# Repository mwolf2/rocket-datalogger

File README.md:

# rocket-datalogger
Linux-based datalogger for amateur rockets. School project by Max Wolf and Emmett Hart.
Goal -- Make a datalogger that enables amateur rockets to act as low-altitude sounding rockets for meteorological and kinematic data.
Current Status -- Done (for now, might reopen at some point in the future); Contributions Welcome! (please make a pull request)

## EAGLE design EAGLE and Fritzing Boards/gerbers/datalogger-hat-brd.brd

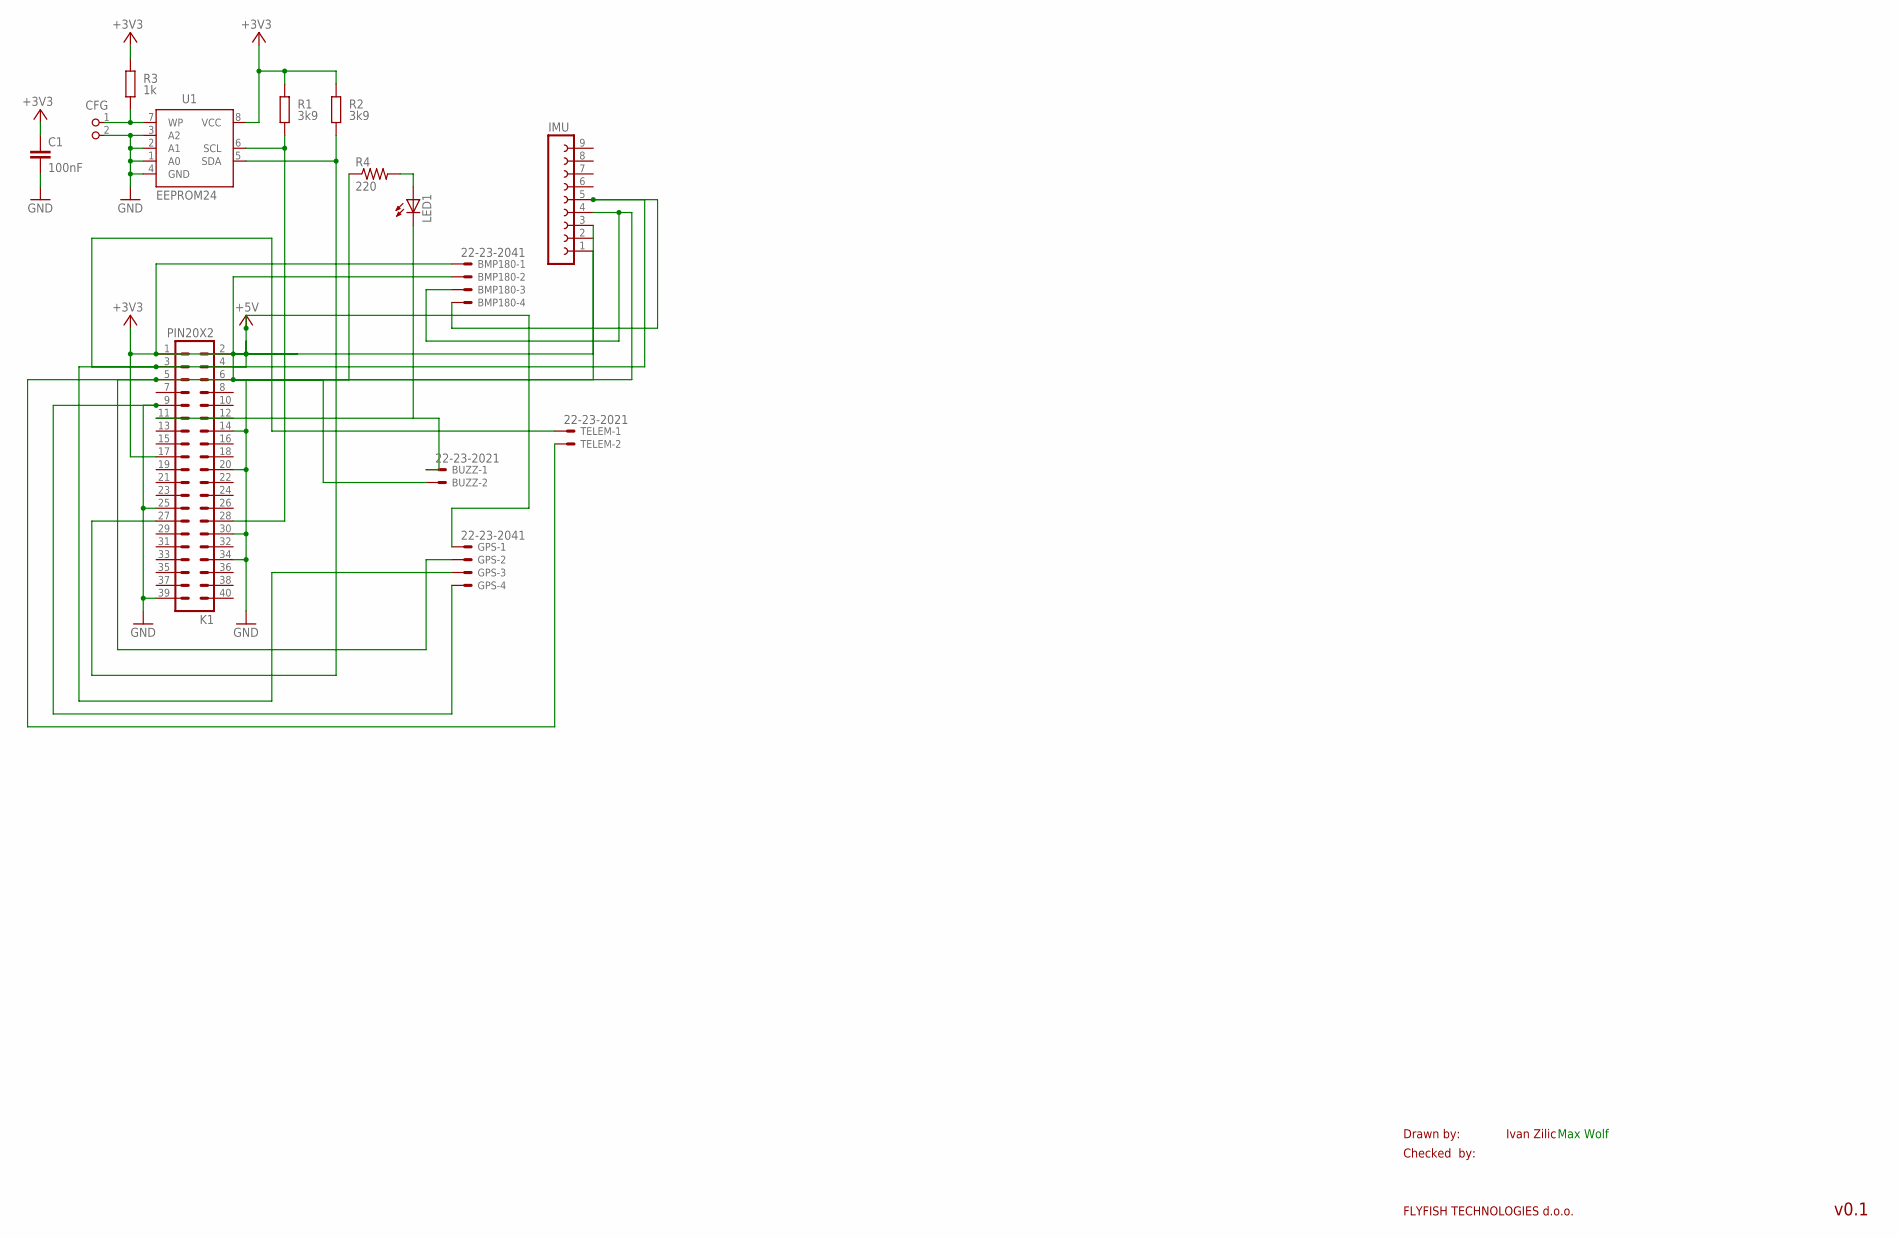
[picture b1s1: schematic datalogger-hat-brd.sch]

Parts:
BMP180: 22-23-2041
BUZZ: 22-23-2021
C1: 100nF; C0805K
CFG: PIN2_100; PIN_W_2
GPS: 22-23-2041
IMU: FE09-1; FE09
K1: PIN20X2; PIN_20X2
LED1: LED_ELD260; LED_LD260
R1, R2: 3k9; M0805; TOLERANCE 5%
R3: 1k; M0805; TOLERANCE 5%
R4: 220; 0204/5
TELEM: 22-23-2021
U1: EEPROM24; SOIC8

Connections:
+3V3: BMP180.1, C1.1, IMU.1, K1.1, K1.17, R1.2, R2.2, R3.2, U1.8 (VCC)
+5V: GPS.1, K1.2, K1.4
GND: BMP180.2, BUZZ.2, C1.2, CFG.2, GPS.4, IMU.3, K1.6, K1.9, K1.14, K1.20, K1.25, K1.30, K1.34, K1.39, R4.1, U1.1 (A0), U1.2 (A1), U1.3 (A2), U1.4 (GND)
unnamed: K1.28, R1.1, U1.6 (SCL)
unnamed: K1.27, R2.1, U1.5 (SDA)
unnamed: CFG.1, R3.1, U1.7 (WP)
unnamed: BMP180.4, GPS.3, IMU.5, K1.3, TELEM.1
unnamed: BMP180.3, GPS.2, IMU.4, K1.5, TELEM.2
unnamed: BUZZ.1, K1.11, LED1.K (C)
unnamed: LED1.A, R4.2

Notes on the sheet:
Drawn by:
Checked by:
FLYFISH TECHNOLOGIES d.o.o.
Ivan Zilic
v0.1
Max Wolf

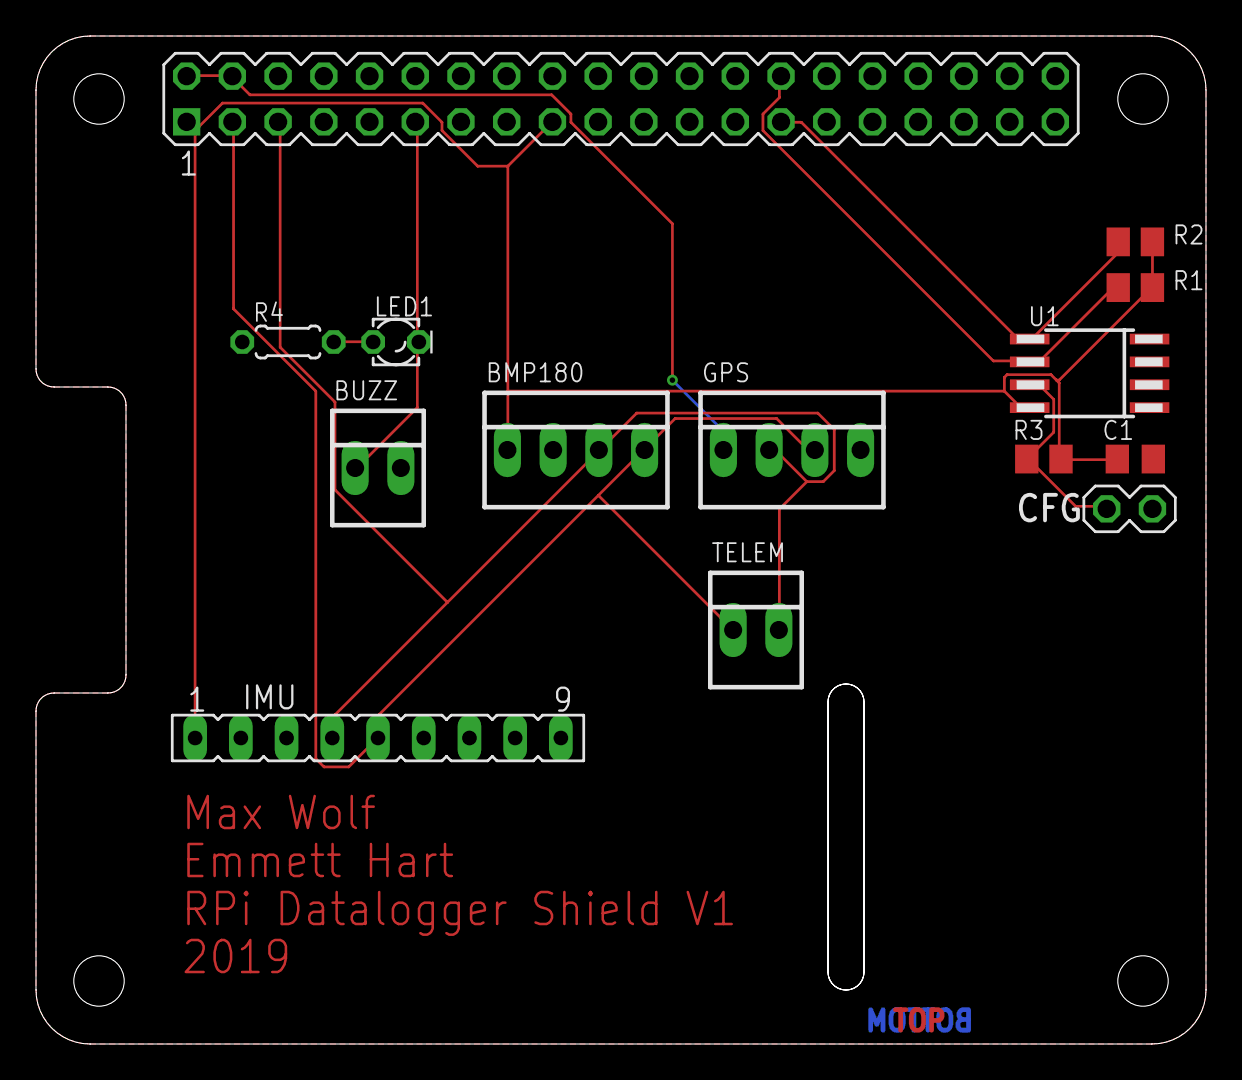
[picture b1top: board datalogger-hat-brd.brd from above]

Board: 2 copper layers, 65.0 x 56.0 mm, 14 parts (0 on the bottom side), 10 nets.

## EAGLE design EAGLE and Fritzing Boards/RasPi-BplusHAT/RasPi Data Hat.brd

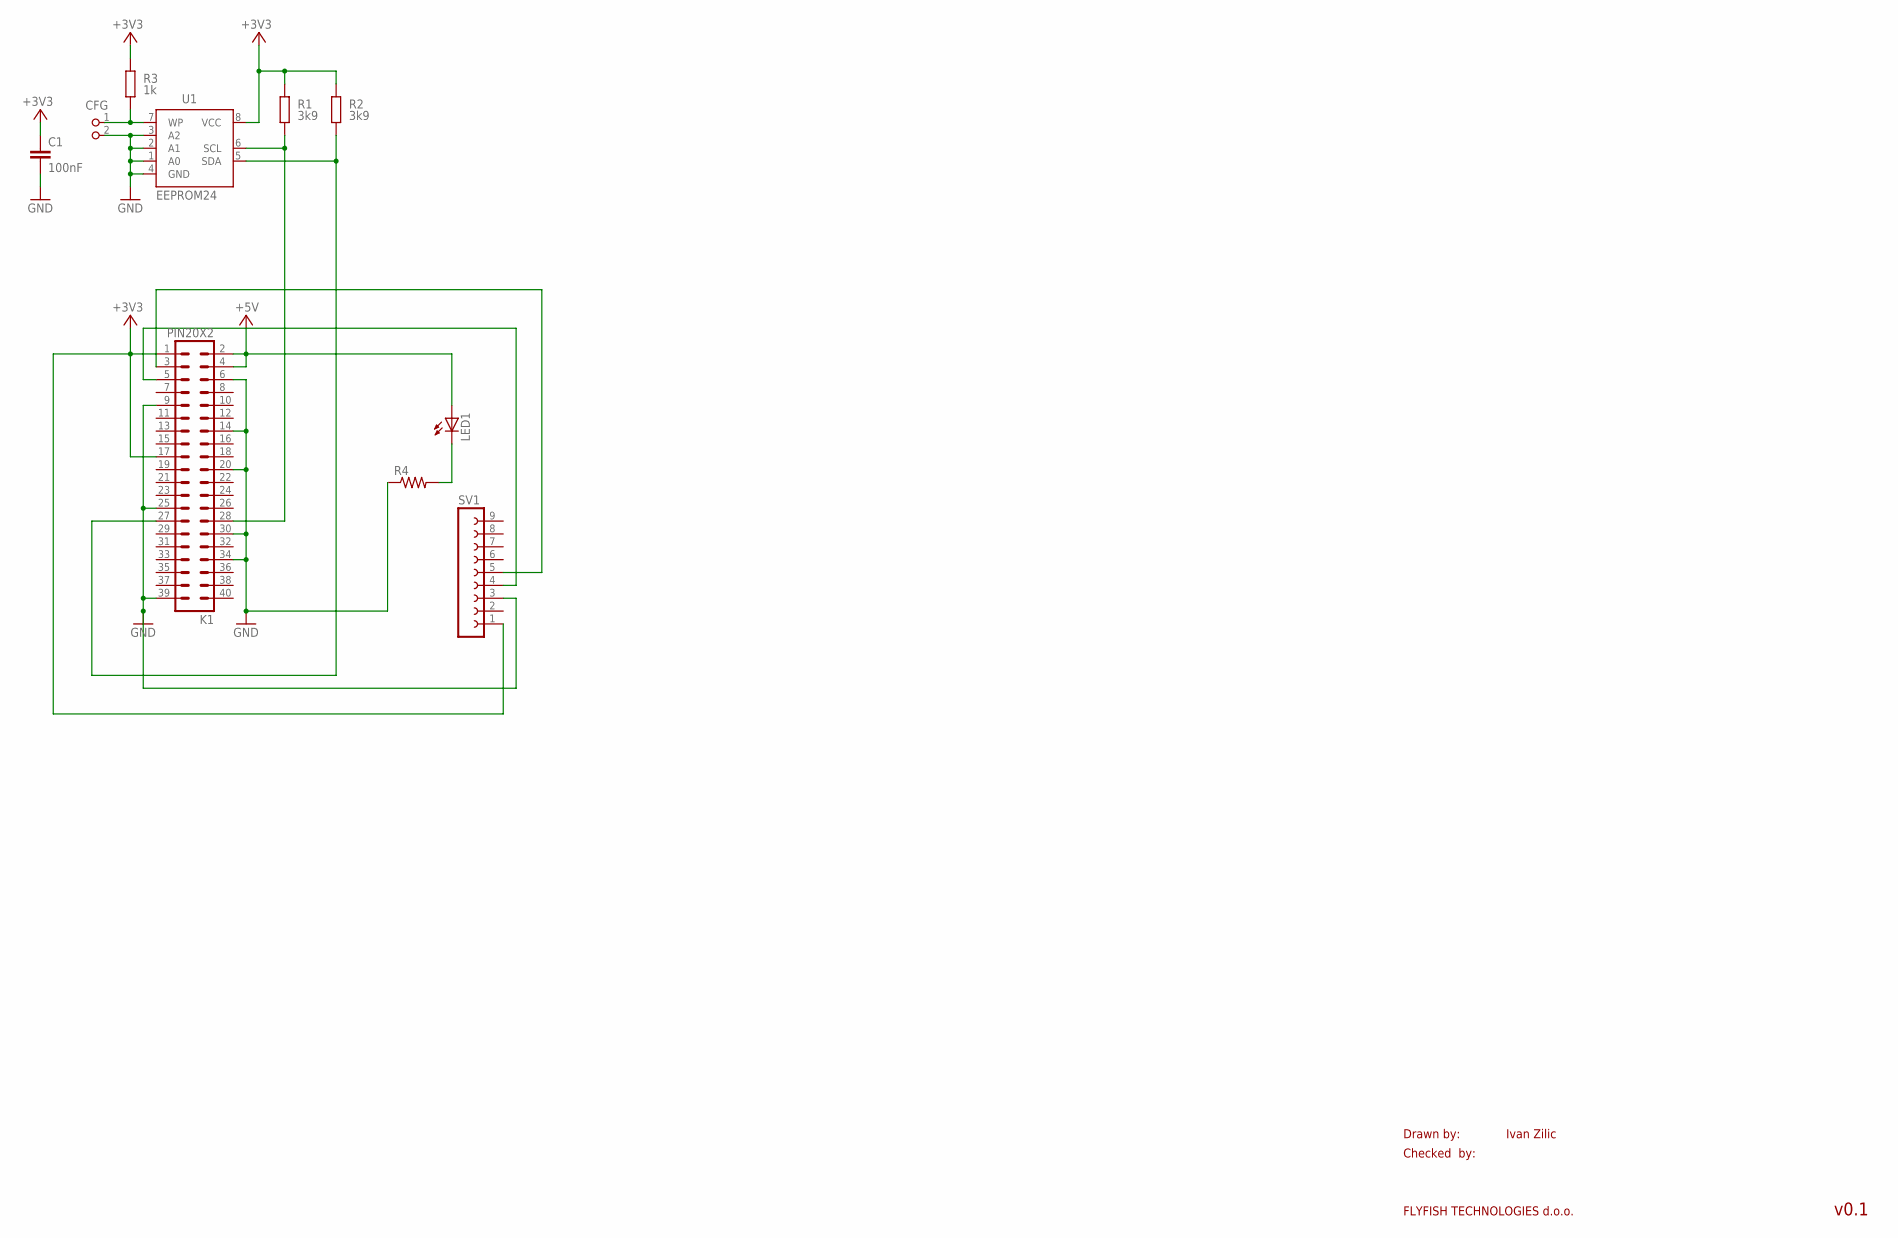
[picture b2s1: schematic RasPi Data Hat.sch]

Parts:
C1: 100nF; C0805K
CFG: PIN2_100; PIN_W_2
K1: PIN20X2; PIN_20X2
LED1: LED3MM
R1, R2: 3k9; M0805; TOLERANCE 5%
R3: 1k; M0805; TOLERANCE 5%
R4: R-US_0204/5; 0204/5
SV1: FE09-1; FE09
U1: EEPROM24; SOIC8

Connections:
+3V3: C1.1, K1.1, K1.17, R1.2, R2.2, R3.2, SV1.1, U1.8 (VCC)
+5V: K1.2, K1.4, LED1.A
GND: C1.2, CFG.2, K1.6, K1.9, K1.14, K1.20, K1.25, K1.30, K1.34, K1.39, R4.1, SV1.3, U1.1 (A0), U1.2 (A1), U1.3 (A2), U1.4 (GND)
unnamed: K1.28, R1.1, U1.6 (SCL)
unnamed: K1.27, R2.1, U1.5 (SDA)
unnamed: CFG.1, R3.1, U1.7 (WP)
unnamed: LED1.K (C), R4.2
unnamed: K1.5, SV1.4
unnamed: K1.3, SV1.5

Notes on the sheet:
Drawn by:
Checked by:
FLYFISH TECHNOLOGIES d.o.o.
Ivan Zilic
v0.1

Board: 2 copper layers, 10 parts (0 on the bottom side), 9 nets, no tracks yet.

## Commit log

2019-04-27 Add files via upload
    First project commit outside of when repository was created. Includes EAGLE and Fritzing boards, images, and programs as of 4/27/2019 at 11:33AM GMT
2019-04-28 Add files via upload
    Committed more recent files to master branch, and not in .zip format. 5:18PM GMT
2019-05-01 Rename EAGLE and Fritzing Boards/copper_bottom.gbr to EAGLE and Fritzing Boards/gerbers/copper_bottom.gbr
2019-05-01 Rename EAGLE and Fritzing Boards/copper_top.gbr to EAGLE and Fritzing Boards/gerbers/copper_top.gbr
2019-05-01 Rename EAGLE and Fritzing Boards/datalogger-hat-brd.brd to EAGLE and Fritzing Boards/gerbers/datalogger-hat-brd.brd
2019-05-01 Rename EAGLE and Fritzing Boards/datalogger-hat-brd.sch to EAGLE and Fritzing Boards/gerbers/datalogger-hat-brd.sch
2019-05-01 Rename EAGLE and Fritzing Boards/drills.xln to EAGLE and Fritzing Boards/gerbers/drills.xln
2019-05-01 Rename EAGLE and Fritzing Boards/gerber_job.gbrjob to EAGLE and Fritzing Boards/gerbers/gerber_job.gbrjob
2019-05-01 Rename EAGLE and Fritzing Boards/profile.gbr to EAGLE and Fritzing Boards/gerbers/profile.gbr
2019-05-01 Rename EAGLE and Fritzing Boards/silkscreen_bottom.gbr to EAGLE and Fritzing Boards/gerbers/silkscreen_bottom.gbr
2019-05-01 Rename EAGLE and Fritzing Boards/silkscreen_top.gbr to EAGLE and Fritzing Boards/gerbers/silkscreen_top.gbr
2019-05-01 Rename EAGLE and Fritzing Boards/soldermask_bottom.gbr to EAGLE and Fritzing Boards/gerbers/soldermask_bottom.gbr
2019-05-01 Rename EAGLE and Fritzing Boards/soldermask_top.gbr to EAGLE and Fritzing Boards/gerbers/soldermask_top.gbr
2019-05-01 Rename EAGLE and Fritzing Boards/solderpaste_bottom.gbr to EAGLE and Fritzing Boards/gerbers/solderpaste_bottom.gbr
2019-05-01 Rename EAGLE and Fritzing Boards/solderpaste_top.gbr to EAGLE and Fritzing Boards/gerbers/solderpaste_top.gbr
2019-05-04 Uploaded first version telemetry sketch.
2019-05-04 Rename sketch_may03d.ino to Arduino/sketch_may03d.ino
2019-05-04 Rename sketch_may03d.ino to groundmodule.ino
2019-05-10 Updated raspberrypi_air_module.py to export CSV File and add lib/
2019-05-10 finished CSV export support, need to fix AGL logging
2019-05-10 Forgot to run program to test after last commit, accidentally removed dependancy, Although I don't think we need that section of code anyways (calibration file)
2019-05-11 added Raspberry Pi case
2019-05-11 Updated pin length
2019-05-18 Fixed directory problems (as long as Pi Programs and lib are next to each other) and added a file of successful data).
2019-05-18 Used data to calculata delta H column
2019-05-19 Started a data analysis file and reference
2019-05-20 Added an Alpha Beta filter and more plots.
